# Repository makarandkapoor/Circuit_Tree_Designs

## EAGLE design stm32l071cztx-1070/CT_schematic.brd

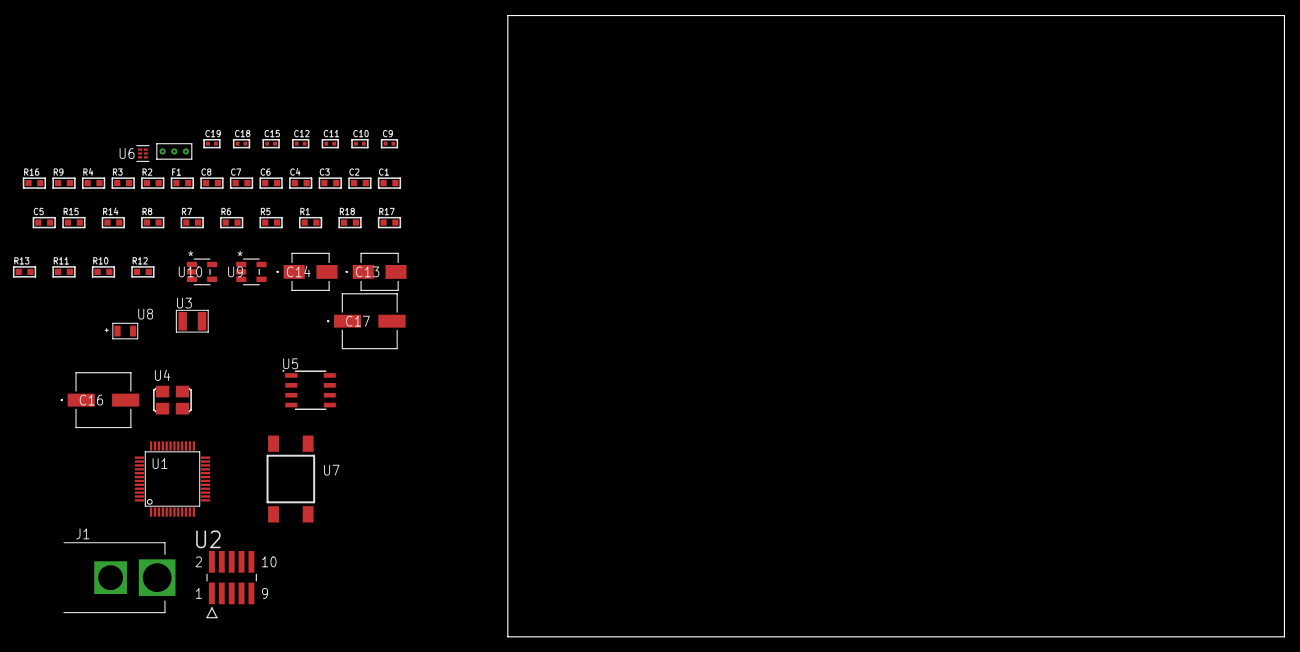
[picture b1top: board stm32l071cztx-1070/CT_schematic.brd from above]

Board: 2 copper layers, 100.0 x 80.0 mm, 50 parts (0 on the bottom side), 24 nets, no tracks yet.

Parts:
C1, C2, C3, C4, C6: 1e-07; C0603
C5: 4.7e-06; C0603
C7: 1e-08; C0603
C8: 1e-06; C0603
C9, C10: 1e-11; C0402
C11, C15: 1e-07; C0402
C12, C18, C19: 1e-08; C0402
C13: 1e-06; EXV-9B
C14: 2.2e-06; EXV-9B
C16, C17: 0.0001; EXV-9H
F1: 240.0; L0603
J1: PJ-037B; PJ-037B_PACKAGE
R1, R5, R6, R7, R8, R14, R15: 10000.0; R0603
R2: 1000.0; R0603
R3: 1600.5; R0603
R4: 4700.0; R0603
R9: 5.0; R0603
R10, R11, R13: 100000.0; R0603
R12: 164658.62; R0603
R16: 9100.0; R0603
R17: 680000.0; R0603
R18: 120000.0; R0603
U1: STM32L071CZT6; LQFP48
U2: FTSH-105-01-L-DV-K; SAMTEC_FTSH-105-01-L-DV-K
U3: ABS07-32.768KHZ-7-T
U4: ASFL1-25MHZ-NCS; ASFL1
U5: LP2954AIMX/NOPB; LP2954
U6: TPS3895ADRYR; SON-6
U7: 4-1437565-2; SW_4-1437565-2
U8: Q65110A2395; LGM67K-G1J2-24-Z
U9, U10: nc7sz125m5x; NC7SZ125M5X
U11: Dummy; DUMMY_PACKAGE_101

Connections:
CLK_CRYSTAL_U1_3: C9.1, U1.3, U3.1
CLK_CRYSTAL_U1_4: C10.1, U1.4, U3.2
CLK_U1_5: U1.5, U4.3
GND: C1.2, C2.2, C3.2, C4.2, C5.2, C6.2, C7.2, C8.2, C9.2, C10.2, C11.2, C12.2, C13.2, C14.2, C15.2, C16.2, C17.2, C18.2, C19.2, J1.2, R2.2, R5.2, R9.2, R13.2, R16.2, R18.2, U1.8, U1.23, U1.35, U1.47, U2.3, U2.5, U4.2, U5.4, U6.2, U8.C, U9.2, U9.3, U10.1, U10.3, U11.1
NET_U1_7: R4.1, U1.7, U10.4
NET_U1_9: C7.1, C8.1, F1.1, U1.9
NET_U1_44: R5.1, U1.44
NET_U1_45: R3.1, U1.45, U8.A
NET_U1_46: R1.1, U1.46, U7.3, U7.4
NET_U2_9: R9.1, U2.9
NET_U5_3: R11.1, U5.3
NET_U5_5: R10.1, U5.5
NET_U5_7: R12.2, R13.1, U5.7
NET_U6_1: R15.1, R16.1, U6.1
NET_U6_3: R17.2, R18.1, U6.3
NET_U6_4: R14.1, U6.4, U9.4, U10.2
NET_U7_1: R2.1, U7.1, U7.2
PROC_ADC_IN3: U1.13, U11.2
PROC_ADC_IN4: U1.14, U11.3
PROC_SYS_SWCLK: R7.1, U1.37, U2.4
PROC_SYS_SWDIO: R8.1, U1.34, U2.2
RST_OUT_U2_JTAG_RST_B: R6.1, U2.10, U9.1
VCC_S1_16V9: C13.1, C16.1, C17.1, J1.1, R11.2, U5.8
VCC_TIER1_3V3: C1.1, C2.1, C3.1, C4.1, C5.1, C6.1, C11.1, C12.1, C14.1, C15.1, C18.1, C19.1, F1.2, R1.2, R3.2, R4.2, R6.2, R7.2, R8.2, R10.2, R12.1, R14.2, R15.2, R17.1, U1.1, U1.24, U1.36, U1.48, U2.1, U4.4, U5.1, U6.6, U9.5, U10.5

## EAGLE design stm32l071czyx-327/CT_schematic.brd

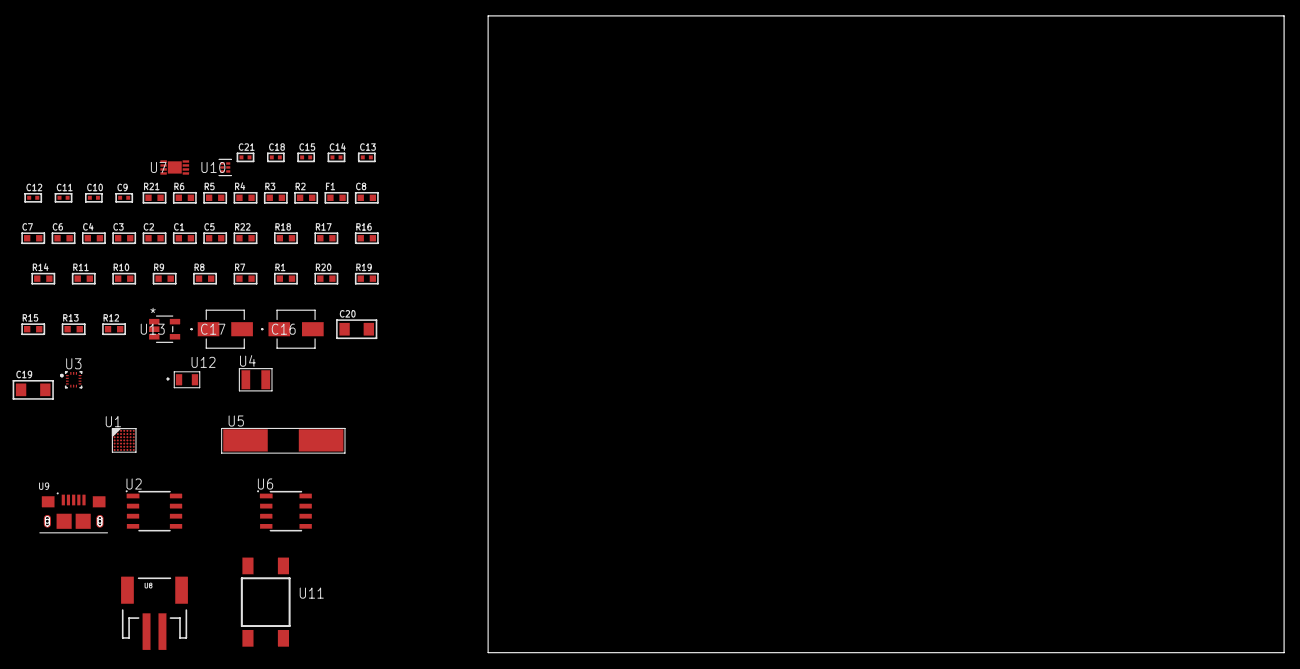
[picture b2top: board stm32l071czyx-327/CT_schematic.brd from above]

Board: 2 copper layers, 155.6 x 80.0 mm, 57 parts (0 on the bottom side), 30 nets, no tracks yet.

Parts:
C1, C2, C3, C4, C6: 1e-07; C0603
C5: 4.7e-06; C0603
C7: 1e-08; C0603
C8: 1e-06; C0603
C9, C10, C11, C12: 1e-11; C0402
C13, C21: 1e-08; C0402
C14, C15, C18: 1e-07; C0402
C16: 1e-06; EXV-9B
C17: 2.2e-06; EXV-9B
C19, C20: 1e-05; C1206
F1: 240.0; L0603
R1, R7, R8, R9, R10, R11, R16, R17, R22: 10000.0; R0603
R2: 1000.0; R0603
R3: 910.0; R0603
R4: 4700.0; R0603
R5, R6: 2200.0; R0603
R12, R13, R15: 100000.0; R0603
R14: 47000.0; R0603
R18: 82000.0; R0603
R19: 300000.0; R0603
R20: 120000.0; R0603
R21: 2000.0; R0603
U1: STM32L071CZY6; WLCSP49
U2: AT25320B-SSHL-T; SOIC-8
U3: BMC150; LGA14R35P5X6_200X200X100
U4: ABS07-32.768KHZ-7-T
U5: ABLS-25.000MHZ-B2F-T
U6: LP2954AIMX/NOPB; LP2954
U7: MCP73831T-2ACI/MC; DFN8_2X3MC
U8: S2B-PH-SM4-TB(LF)(SN); JST-2-SMD
U9: 10118193-0001LF; FCI_10118193-0001LF
U10: TPS3895ADRYR; SON-6
U11: 4-1437565-2; SW_4-1437565-2
U12: Q65110A2395; LGM67K-G1J2-24-Z
U13: nc7sz125m5x; NC7SZ125M5X

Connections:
CLK_CRYSTAL_U1_C6: C9.1, U1.C6, U4.1
CLK_CRYSTAL_U1_C7: C10.1, U1.C7, U4.2
CLK_CRYSTAL_U1_D6: C11.1, U1.D6, U5.1
CLK_CRYSTAL_U1_D7: C12.1, U1.D7, U5.2
GND: C1.2, C2.2, C3.2, C4.2, C5.2, C6.2, C7.2, C8.2, C9.2, C10.2, C11.2, C12.2, C13.2, C14.2, C15.2, C16.2, C17.2, C18.2, C19.2, C20.2, C21.2, R2.2, R7.2, R15.2, R18.2, R20.2, R21.2, U1.D4, U2.4, U3.1, U3.6, U3.7, U3.9, U6.4, U7.6, U7.9, U8.2, U9.5, U9.6, U9.7, U9.8, U9.9, U10.2, U12.C, U13.1, U13.3
INPUT_USBPOWER_5V: C19.1, R22.2, U7.1, U7.2, U9.1
NET_U1_A5: R7.1, U1.A5
NET_U1_A6: R6.1, U1.A6, U3.14
NET_U1_B4: R5.1, U1.B4, U3.11
NET_U1_D5: R4.1, U1.D5, U13.4
NET_U1_F7: C7.1, C8.1, F1.1, U1.E6, U1.F7
NET_U1_G6: R3.1, U1.G6, U12.A
NET_U1_G7: R1.1, U1.G7, U11.3, U11.4
NET_U2_3: R8.1, U2.3
NET_U2_7: R10.1, U2.7
NET_U6_3: R13.1, U6.3
NET_U6_5: R12.1, U6.5
NET_U6_7: R14.2, R15.1, U6.7
NET_U7_5: R22.1, U7.5
NET_U7_8: R21.1, U7.8
NET_U10_1: R17.1, R18.1, U10.1
NET_U10_3: R19.2, R20.1, U10.3
NET_U10_4: R16.1, U10.4, U13.2
NET_U11_1: R2.1, U11.1, U11.2
PROC_SPI1_MISO: U1.B3, U2.2
PROC_SPI1_MOSI: U1.A4, U2.5
PROC_SPI1_NSS: R9.1, U1.A2, U2.1
PROC_SPI1_SCK: U1.A3, U2.6
VCC_S1_3V7: C16.1, C20.1, R13.2, U6.8, U7.3, U7.4, U8.1
VCC_TIER1_1V8: C1.1, C2.1, C3.1, C4.1, C5.1, C6.1, C13.1, C14.1, C15.1, C17.1, C18.1, C21.1, F1.2, R1.2, R3.2, R4.2, R5.2, R6.2, R8.2, R9.2, R10.2, R11.1, R11.2, R12.2, R14.1, R16.2, R17.2, R19.1, U1.A1, U1.A7, U1.B6, U1.G2, U2.8, U3.8, U3.10, U3.12, U3.13, U6.1, U10.6, U13.5

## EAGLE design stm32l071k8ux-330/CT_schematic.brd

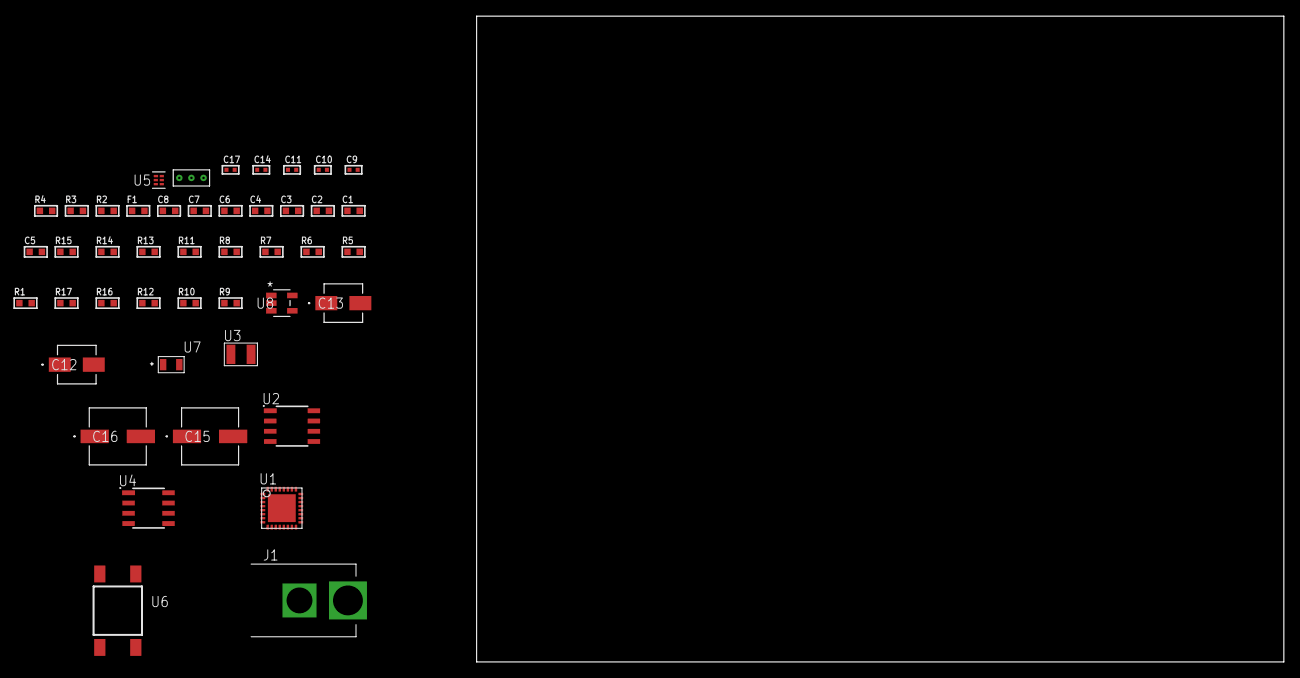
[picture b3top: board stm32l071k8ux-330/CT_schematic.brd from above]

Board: 2 copper layers, 100.0 x 80.0 mm, 45 parts (0 on the bottom side), 25 nets, no tracks yet.

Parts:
C1, C2, C3, C4, C6: 1e-07; C0603
C5: 4.7e-06; C0603
C7: 1e-08; C0603
C8: 1e-06; C0603
C9, C10: 1e-11; C0402
C11, C17: 1e-08; C0402
C12: 1e-06; EXV-9B
C13: 2.2e-06; EXV-9B
C14: 1e-07; C0402
C15, C16: 0.0001; EXV-9H
F1: 240.0; L0603
J1: PJ-037B; PJ-037B_PACKAGE
R1, R5, R6, R7, R8, R13, R14: 10000.0; R0603
R2: 1000.0; R0603
R3: 910.0; R0603
R4: 4700.0; R0603
R9, R10, R12: 100000.0; R0603
R11: 47000.0; R0603
R15: 82000.0; R0603
R16: 300000.0; R0603
R17: 120000.0; R0603
U1: STM32L071K8U6; UFQFPN32
U2: AT25512N-SH-T; SOIC-8
U3: ABS07-32.768KHZ-7-T
U4: LP2954AIMX/NOPB; LP2954
U5: TPS3895ADRYR; SON-6
U6: 4-1437565-2; SW_4-1437565-2
U7: Q65110A2395; LGM67K-G1J2-24-Z
U8: nc7sz125m5x; NC7SZ125M5X
U9: Dummy; DUMMY_PACKAGE_90

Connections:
CLK_CRYSTAL_U1_1: C9.1, U1.1, U3.1
CLK_CRYSTAL_U1_2: C10.1, U1.2, U3.2
GND: C1.2, C2.2, C3.2, C4.2, C5.2, C6.2, C7.2, C8.2, C9.2, C10.2, C11.2, C12.2, C13.2, C14.2, C15.2, C16.2, C17.2, J1.2, R2.2, R5.2, R12.2, R15.2, R17.2, U1.4, U1.16, U1.31, U1.EPAD, U2.4, U4.4, U5.2, U7.C, U8.1, U8.3, U9.1
NET_U1_3: R4.1, U1.3, U8.4
NET_U1_5: C7.1, C8.1, F1.1, U1.5
NET_U1_28: R3.1, U1.28, U7.A
NET_U1_29: R1.1, U1.29, U6.3, U6.4
NET_U1_30: R5.1, U1.30
NET_U2_3: R6.1, U2.3
NET_U2_7: R8.1, U2.7
NET_U4_3: R10.1, U4.3
NET_U4_5: R9.1, U4.5
NET_U4_7: R11.2, R12.1, U4.7
NET_U5_1: R14.1, R15.1, U5.1
NET_U5_3: R16.2, R17.1, U5.3
NET_U5_4: R13.1, U5.4, U8.2
NET_U6_1: R2.1, U6.1, U6.2
PROC_ADC_IN1: U1.7, U9.3
PROC_ADC_IN9: U1.15, U9.2
PROC_SPI1_MISO: U1.12, U2.2
PROC_SPI1_MOSI: U1.13, U2.5
PROC_SPI1_NSS: R7.1, U1.10, U2.1
PROC_SPI1_SCK: U1.11, U2.6
VCC_S1_16V2: C12.1, C15.1, C16.1, J1.1, R10.2, U4.8
VCC_TIER1_1V8: C1.1, C2.1, C3.1, C4.1, C5.1, C6.1, C11.1, C13.1, C14.1, C17.1, F1.2, R1.2, R3.2, R4.2, R6.2, R7.2, R8.2, R9.2, R11.1, R13.2, R14.2, R16.1, U1.17, U1.24, U1.32, U2.8, U4.1, U5.6, U8.5

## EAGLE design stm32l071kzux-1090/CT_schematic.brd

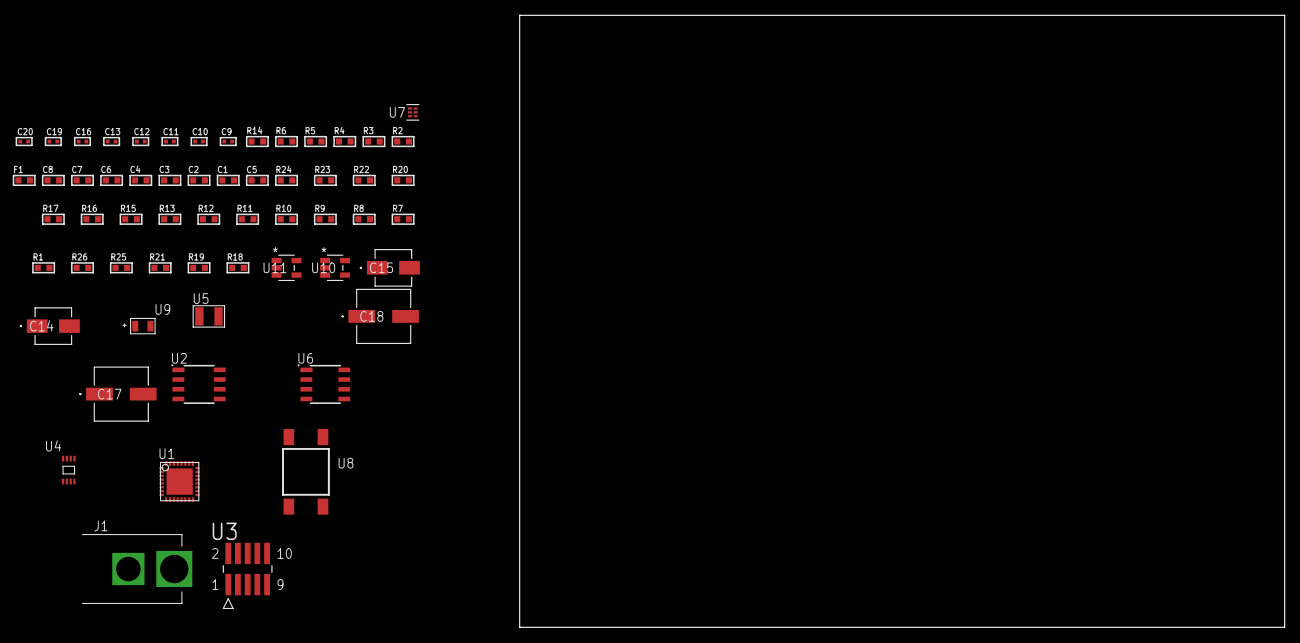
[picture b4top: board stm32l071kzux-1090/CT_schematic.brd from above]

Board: 2 copper layers, 100.0 x 80.0 mm, 59 parts (0 on the bottom side), 32 nets, no tracks yet.

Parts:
C1, C2, C3, C4, C6: 1e-07; C0603
C5: 4.7e-06; C0603
C7: 1e-08; C0603
C8: 1e-06; C0603
C9, C10: 1e-11; C0402
C11, C13, C19, C20: 1e-08; C0402
C12, C16: 1e-07; C0402
C14: 1e-06; EXV-9B
C15: 2.2e-06; EXV-9B
C17, C18: 0.0001; EXV-9H
F1: 240.0; L0603
J1: PJ-037B; PJ-037B_PACKAGE
R1, R7, R8, R9, R10, R11, R12, R13, R15, R16, R17, R22, R23: 10000.0; R0603
R2: 1000.0; R0603
R3: 910.0; R0603
R4: 4700.0; R0603
R5, R6: 2200.0; R0603
R14: 5.0; R0603
R18, R19, R21: 100000.0; R0603
R20: 47000.0; R0603
R24: 82000.0; R0603
R25: 300000.0; R0603
R26: 120000.0; R0603
U1: STM32L071KZU6; UFQFPN32
U2: AT25640B-SSHL-T; SOIC-8
U3: FTSH-105-01-L-DV-K; SAMTEC_FTSH-105-01-L-DV-K
U4: 24AA128T-I/MNY; TDFN-8/6MM
U5: ABS07-32.768KHZ-7-T
U6: LP2954AIMX/NOPB; LP2954
U7: TPS3895ADRYR; SON-6
U8: 4-1437565-2; SW_4-1437565-2
U9: Q65110A2395; LGM67K-G1J2-24-Z
U10, U11: nc7sz125m5x; NC7SZ125M5X

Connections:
CLK_CRYSTAL_U1_1: C9.1, U1.1, U5.1
CLK_CRYSTAL_U1_2: C10.1, U1.2, U5.2
GND: C1.2, C2.2, C3.2, C4.2, C5.2, C6.2, C7.2, C8.2, C9.2, C10.2, C11.2, C12.2, C13.2, C14.2, C15.2, C16.2, C17.2, C18.2, C19.2, C20.2, J1.2, R2.2, R7.2, R14.2, R15.2, R17.2, R21.2, R24.2, R26.2, U1.4, U1.16, U1.31, U1.EPAD, U2.4, U3.3, U3.5, U4.4, U4.7, U6.4, U7.2, U9.C, U10.2, U10.3, U11.1, U11.3
NET_U1_3: R4.1, U1.3, U11.4
NET_U1_5: C7.1, C8.1, F1.1, U1.5
NET_U1_19: R5.1, U1.19, U4.6
NET_U1_20: R6.1, U1.20, U4.5
NET_U1_28: R3.1, U1.28, U9.A
NET_U1_29: R1.1, U1.29, U8.3, U8.4
NET_U1_30: R7.1, U1.30
NET_U2_3: R8.1, U2.3
NET_U2_7: R10.1, U2.7
NET_U3_9: R14.1, U3.9
NET_U4_1: R15.1, U4.1
NET_U4_2: R16.1, U4.2
NET_U4_3: R17.1, U4.3
NET_U6_3: R19.1, U6.3
NET_U6_5: R18.1, U6.5
NET_U6_7: R20.2, R21.1, U6.7
NET_U7_1: R23.1, R24.1, U7.1
NET_U7_3: R25.2, R26.1, U7.3
NET_U7_4: R22.1, U7.4, U10.4, U11.2
NET_U8_1: R2.1, U8.1, U8.2
PROC_SPI1_MISO: U1.12, U2.2
PROC_SPI1_MOSI: U1.13, U2.5
PROC_SPI1_NSS: R9.1, U1.10, U2.1
PROC_SPI1_SCK: U1.11, U2.6
PROC_SYS_SWCLK: R12.1, U1.25, U3.4
PROC_SYS_SWDIO: R13.1, U1.23, U3.2
RST_OUT_U3_JTAG_RST_B: R11.1, U3.10, U10.1
VCC_S1_4V7: C14.1, C17.1, C18.1, J1.1, R19.2, U6.8
VCC_TIER1_1V8: C1.1, C2.1, C3.1, C4.1, C5.1, C6.1, C11.1, C12.1, C13.1, C15.1, C16.1, C19.1, C20.1, F1.2, R1.2, R3.2, R4.2, R5.2, R6.2, R8.2, R9.2, R10.2, R11.2, R12.2, R13.2, R16.2, R18.2, R20.1, R22.2, R23.2, R25.1, U1.17, U1.24, U1.32, U2.8, U3.1, U4.8, U6.1, U7.6, U10.5, U11.5

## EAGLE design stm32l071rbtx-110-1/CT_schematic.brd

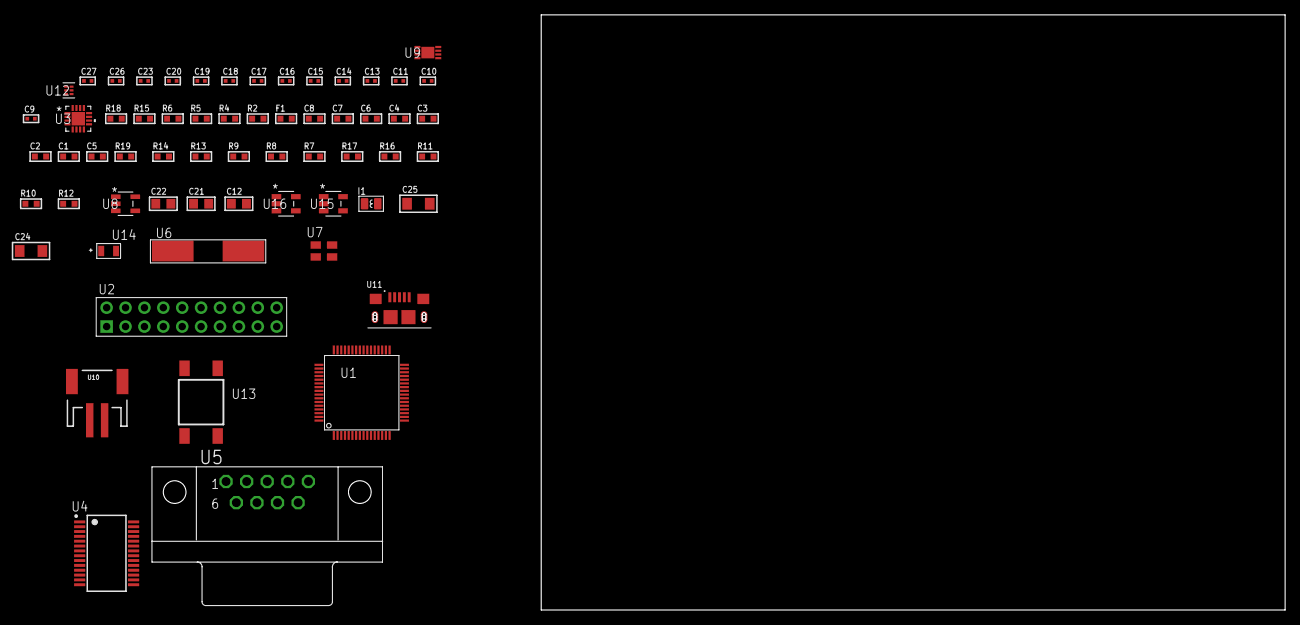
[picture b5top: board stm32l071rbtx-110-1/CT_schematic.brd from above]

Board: 2 copper layers, 122.6 x 80.0 mm, 62 parts (0 on the bottom side), 42 nets, no tracks yet.

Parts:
C1, C2, C3, C4, C6: 1e-07; C0603
C5: 4.7e-06; C0603
C7: 1e-08; C0603
C8: 1e-06; C0603
C9, C10: 1e-11; C0402
C11, C13, C14, C15, C16, C17, C18, C19, C23: 1e-07; C0402
C12: 4.7e-06; C0805
C20, C26, C27: 1e-08; C0402
C21, C22: 1e-05; C0805
C24, C25: 1e-05; C1206
F1: 240.0; L0603
I1: 3.3e-06; L0806
R2: 1000.0; R0603
R4: 4700.0; R0603
R5, R6: 2200.0; R0603
R7, R8, R9, R13, R14, R19: 10000.0; R0603
R10: 100000.0; R0603
R11: 220000.0; R0603
R12: 1000000.0; R0603
R15: 9100.0; R0603
R16: 680000.0; R0603
R17: 120000.0; R0603
R18: 2000.0; R0603
U1: STM32L071RBT6; LQFP64
U2: TST-110-05-T-D-RA
U3: MMA8451QT; QFN-16
U4: ST3241EBPR; SSOP-28
U5: 182-009-113R531; 182-009-MALE
U6: ABLS-25.000MHZ-B2F-T
U7: ASEK-32.768KHz-ECST; ASEK
U8: ltc3406es5; TSOT-23-5
U9: MCP73831T-2ACI/MC; DFN8_2X3MC
U10: S2B-PH-SM4-TB(LF)(SN); JST-2-SMD
U11: 10118193-0001LF; FCI_10118193-0001LF
U12: TPS3895ADRYR; SON-6
U13: 4-1437565-2; SW_4-1437565-2
U14: Q65110A2395; LGM67K-G1J2-24-Z
U15, U16: nc7sz125m5x; NC7SZ125M5X

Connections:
CLK_CRYSTAL_U1_5: C9.1, U1.5, U6.1
CLK_CRYSTAL_U1_6: C10.1, U1.6, U6.2
CLK_U1_3: U1.3, U7.3
GND: C1.2, C2.2, C3.2, C4.2, C5.2, C6.2, C7.2, C8.2, C9.2, C10.2, C11.2, C12.2, C13.2, C14.2, C15.2, C18.2, C19.2, C20.2, C21.2, C22.1, C22.2, C23.2, C24.2, C25.2, C26.2, C27.2, R2.2, R7.2, R11.2, R15.2, R17.2, R18.2, U1.12, U1.18, U1.31, U1.47, U1.63, U2.4, U2.6, U2.8, U2.10, U2.12, U2.14, U2.16, U2.18, U2.20, U3.5, U3.10, U3.12, U3.17, U4.23, U4.25, U5.5, U7.2, U8.2, U9.6, U9.9, U10.2, U11.5, U11.6, U11.7, U11.8, U11.9, U12.2, U14.C, U15.2, U15.3, U16.1, U16.3
INPUT_USBPOWER_5V: C24.1, R19.2, U9.1, U9.2, U11.1
NET_U1_7: R4.1, U1.7, U16.4
NET_U1_13: C7.1, C8.1, F1.1, U1.13
NET_U1_42: R5.1, U1.42, U3.4
NET_U1_43: R6.1, U1.43, U3.6
NET_U1_60: R7.1, U1.60
NET_U1_62: U13.3, U13.4
NET_U3_2: C14.1, U3.2
NET_U3_7: R9.1, U3.7
NET_U4_1: C17.1, U4.1
NET_U4_2: C17.2, U4.2
NET_U4_3: C19.1, U4.3
NET_U4_22: R10.1, U4.22
NET_U4_24: C16.2, U4.24
NET_U4_27: C18.1, U4.27
NET_U4_28: C16.1, U4.28
NET_U5_2: U4.4, U5.2
NET_U5_3: U4.9, U5.3
NET_U5_7: U4.5, U5.7
NET_U5_8: U4.10, U5.8
NET_U8_3: I1.1, U8.3
NET_U8_5: R11.1, R12.1, U8.5
NET_U8_ATNET_3: I1.2, R12.2
NET_U9_5: R19.1, U9.5
NET_U9_8: R18.1, U9.8
NET_U12_1: R14.1, R15.1, U12.1
NET_U12_3: R16.2, R17.1, U12.3
NET_U12_4: R13.1, U12.4, U15.4, U16.2
NET_U13_1: R2.1, U13.1, U13.2
PROC_LPUART1_CTS: U1.22, U4.13
PROC_LPUART1_RTS: U1.27, U4.18
PROC_LPUART1_RX: U1.8, U4.19
PROC_LPUART1_TX: U1.9, U4.14
PROC_SYS_SWCLK: U1.49, U2.9
PROC_SYS_SWDIO: U1.46, U2.7
RST_OUT_U2_SRESET_B: R8.1, U2.15, U15.1
VCC_S1_3V7: C21.1, C25.1, U8.4, U9.3, U9.4, U10.1
VCC_TIER1_3V3: C1.1, C2.1, C3.1, C4.1, C5.1, C6.1, C11.1, C12.1, C13.1, C15.1, C20.1, C22.2, C23.1, C26.1, C27.1, F1.2, I1.2, R4.2, R5.2, R6.2, R8.2, R9.2, R10.2, R12.2, R13.2, R14.2, R16.1, U1.1, U1.19, U1.32, U1.48, U1.64, U2.1, U3.1, U3.14, U4.26, U7.4, U12.6, U15.5, U16.5

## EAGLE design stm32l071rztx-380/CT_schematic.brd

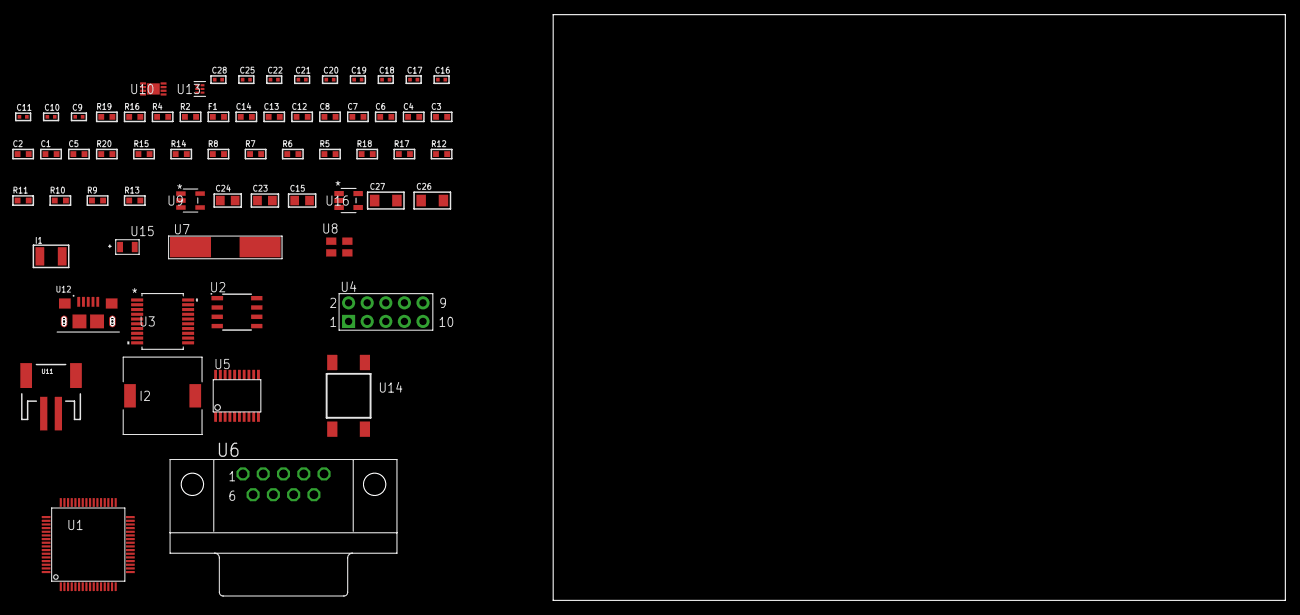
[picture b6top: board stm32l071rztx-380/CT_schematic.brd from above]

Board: 2 copper layers, 167.1 x 80.0 mm, 65 parts (0 on the bottom side), 56 nets, no tracks yet.

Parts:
C1, C2, C3, C4, C6: 1e-07; C0603
C5: 4.7e-06; C0603
C7: 1e-08; C0603
C8, C12, C13, C14: 1e-06; C0603
C9, C10: 1e-11; C0402
C11, C22, C28: 1e-08; C0402
C15: 4.7e-06; C0805
C16, C17, C18, C19, C20, C21, C25: 1e-07; C0402
C23, C24: 1e-05; C0805
C26, C27: 1e-05; C1206
F1: 240.0; L0603
I1: 1.5e-05; L1210
I2: 3.8e-06; DR1040
R2: 1000.0; R0603
R4: 4700.0; R0603
R5, R6, R7, R8, R14, R15, R20: 10000.0; R0603
R9, R10, R11: 100000.0; R0603
R12: 220000.0; R0603
R13: 1000000.0; R0603
R16: 9100.0; R0603
R17: 680000.0; R0603
R18: 120000.0; R0603
R19: 2000.0; R0603
U1: STM32L071RZT6; LQFP64
U2: AT25010B-SSHL-T; SOIC-8
U3: MAX3218EAP+T; SSOP-20
U4: HTSS-105-01-G-D
U5: SP3203ECY-L/TR; TSSOP20-I
U6: 182-009-113R531; 182-009-MALE
U7: ABLS-25.000MHZ-B2F-T
U8: ASEK-32.768KHz-ECST; ASEK
U9: ltc3406es5; TSOT-23-5
U10: MCP73831T-2ACI/MC; DFN8_2X3MC
U11: S2B-PH-SM4-TB(LF)(SN); JST-2-SMD
U12: 10118193-0001LF; FCI_10118193-0001LF
U13: TPS3895ADRYR; SON-6
U14: 4-1437565-2; SW_4-1437565-2
U15: Q65110A2395; LGM67K-G1J2-24-Z
U16: nc7sz125m5x; NC7SZ125M5X

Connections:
CLK_CRYSTAL_U1_5: C9.1, U1.5, U7.1
CLK_CRYSTAL_U1_6: C10.1, U1.6, U7.2
CLK_U1_3: U1.3, U8.3
GND: C1.2, C2.2, C3.2, C4.2, C5.2, C6.2, C7.2, C8.2, C9.2, C10.2, C11.2, C12.2, C13.2, C14.2, C16.2, C17.2, C20.2, C21.2, C22.2, C23.2, C24.1, C24.2, C25.2, C26.2, C27.2, C28.2, R2.2, R5.2, R12.2, R16.2, R18.2, R19.2, U1.12, U1.18, U1.31, U1.47, U1.63, U2.4, U3.5, U3.17, U3.20, U4.9, U5.18, U6.5, U8.2, U9.2, U10.6, U10.9, U11.2, U12.5, U12.6, U12.7, U12.8, U12.9, U13.2, U15.C, U16.1, U16.3
INPUT_USBPOWER_5V: C26.1, R20.2, U10.1, U10.2, U12.1
NET_U1_7: R4.1, U1.7, U16.4
NET_U1_13: C7.1, C8.1, F1.1, U1.13
NET_U1_60: R5.1, U1.60
NET_U1_62: U14.3, U14.4
NET_U2_3: R6.1, U2.3
NET_U2_7: R8.1, U2.7
NET_U3_1: I1.1, U3.1
NET_U3_2: R9.1, U3.2
NET_U3_3: R10.1, U3.3
NET_U3_4: R11.1, U3.4
NET_U3_15: C14.1, U3.15
NET_U3_16: C15.2, U3.16
NET_U3_18: C15.1, U3.18
NET_U3_19: C13.1, U3.19
NET_U4_3: U3.12, U4.3
NET_U4_4: U3.11, U4.4
NET_U4_5: U3.14, U4.5
NET_U4_6: U3.13, U4.6
NET_U5_1: C18.1, U5.1
NET_U5_2: C20.1, U5.2
NET_U5_3: C18.2, U5.3
NET_U5_4: C19.1, U5.4
NET_U5_5: C19.2, U5.5
NET_U5_6: C21.1, U5.6
NET_U6_2: U5.14, U6.2
NET_U6_3: U5.17, U6.3
NET_U6_7: U5.13, U6.7
NET_U6_8: U5.16, U6.8
NET_U9_3: I2.1, U9.3
NET_U9_5: R12.1, R13.1, U9.5
NET_U9_ATNET_3: I2.2, R13.2
NET_U10_5: R20.1, U10.5
NET_U10_8: R19.1, U10.8
NET_U13_1: R15.1, R16.1, U13.1
NET_U13_3: R17.2, R18.1, U13.3
NET_U13_4: R14.1, U13.4, U16.2
NET_U14_1: R2.1, U14.1, U14.2
PROC_LPUART1_CTS: U1.22, U3.8
PROC_LPUART1_RTS: U1.27, U3.10
PROC_LPUART1_RX: U1.8, U3.9
PROC_LPUART1_TX: U1.9, U3.7
PROC_SPI1_MISO: U1.56, U2.2
PROC_SPI1_MOSI: U1.23, U2.5
PROC_SPI1_NSS: R7.1, U1.20, U2.1
PROC_SPI1_SCK: U1.21, U2.6
PROC_USART1_CTS: U1.44, U5.8
PROC_USART1_RTS: U1.45, U5.10
PROC_USART1_RX: U1.43, U5.11
PROC_USART1_TX: U1.42, U5.7
VCC_S1_3V7: C23.1, C27.1, U9.4, U10.3, U10.4, U11.1
VCC_TIER1_3V3: C1.1, C2.1, C3.1, C4.1, C5.1, C6.1, C11.1, C12.1, C16.1, C17.1, C22.1, C24.2, C25.1, C28.1, F1.2, I1.2, I2.2, R4.2, R6.2, R7.2, R8.2, R9.2, R10.2, R11.2, R13.2, R14.2, R15.2, R17.1, U1.1, U1.19, U1.32, U1.48, U1.64, U2.8, U3.6, U5.12, U5.19, U8.4, U13.6, U16.5

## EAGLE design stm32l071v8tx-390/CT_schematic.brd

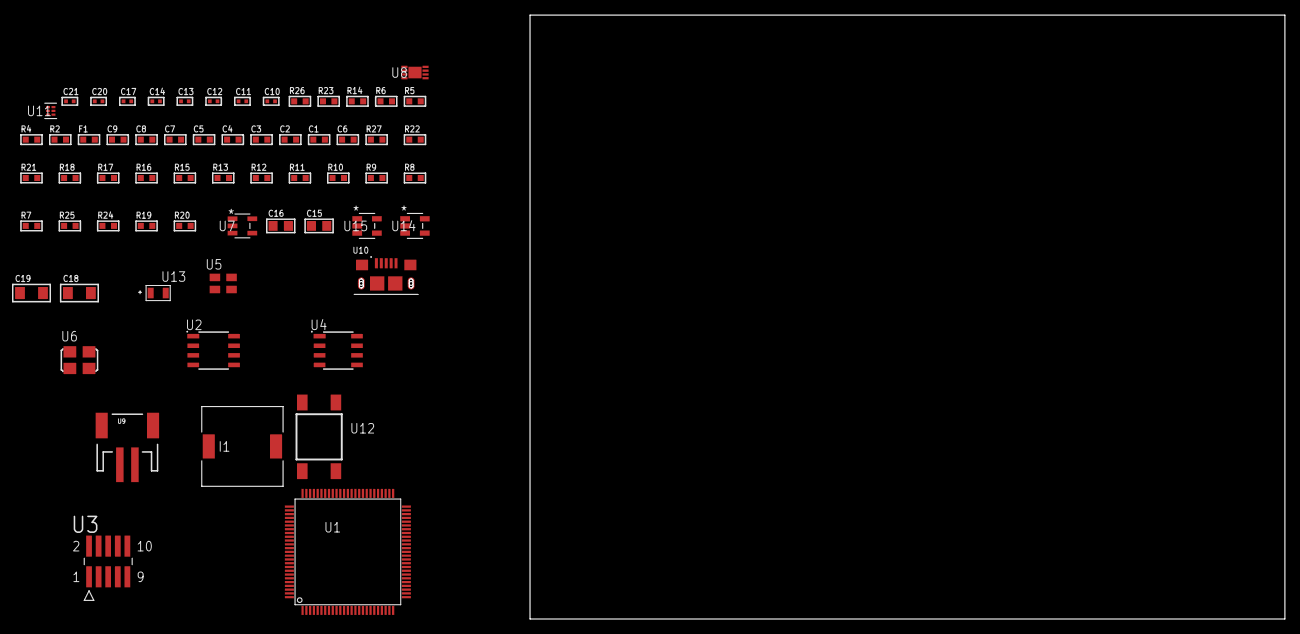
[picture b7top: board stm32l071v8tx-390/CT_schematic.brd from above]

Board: 2 copper layers, 122.6 x 80.0 mm, 63 parts (0 on the bottom side), 35 nets, no tracks yet.

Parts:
C1, C2, C3, C4, C5, C7: 1e-07; C0603
C6: 4.7e-06; C0603
C8: 1e-08; C0603
C9: 1e-06; C0603
C10, C12, C13, C14, C20, C21: 1e-08; C0402
C11, C17: 1e-07; C0402
C15, C16: 1e-05; C0805
C18, C19: 1e-05; C1206
F1: 240.0; L0603
I1: 3.8e-06; DR1040
R2: 1000.0; R0603
R4: 4700.0; R0603
R5, R6: 2200.0; R0603
R7, R8, R9, R10, R11, R12, R13, R15, R16, R17, R18, R21, R22, R27: 10000.0; R0603
R14: 5.0; R0603
R19: 220000.0; R0603
R20: 1000000.0; R0603
R23: 9100.0; R0603
R24: 680000.0; R0603
R25: 120000.0; R0603
R26: 2000.0; R0603
U1: STM32L071V8T6; LQFP100
U2: AT25256B-SSHL-T; SOIC-8
U3: FTSH-105-01-L-DV-K; SAMTEC_FTSH-105-01-L-DV-K
U4: AT24C02D-SSHM-T; AT24C02D
U5: ASEK-32.768KHz-ECST; ASEK
U6: ASFL1-25MHZ-NCS; ASFL1
U7: ltc3406es5; TSOT-23-5
U8: MCP73831T-2ACI/MC; DFN8_2X3MC
U9: S2B-PH-SM4-TB(LF)(SN); JST-2-SMD
U10: 10118193-0001LF; FCI_10118193-0001LF
U11: TPS3895ADRYR; SON-6
U12: 4-1437565-2; SW_4-1437565-2
U13: Q65110A2395; LGM67K-G1J2-24-Z
U14, U15: nc7sz125m5x; NC7SZ125M5X

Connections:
CLK_U1_8: U1.8, U5.3
CLK_U1_12: U1.12, U6.3
GND: C1.2, C2.2, C3.2, C4.2, C5.2, C6.2, C7.2, C8.2, C9.2, C10.2, C11.2, C12.2, C13.2, C14.2, C15.2, C16.1, C16.2, C17.2, C18.2, C19.2, C20.2, C21.2, R2.2, R7.2, R14.2, R15.2, R17.2, R18.2, R19.2, R23.2, R25.2, R26.2, U1.19, U1.20, U1.27, U1.49, U1.74, U1.99, U2.4, U3.3, U3.5, U4.4, U5.2, U6.2, U7.2, U8.6, U8.9, U9.2, U10.5, U10.6, U10.7, U10.8, U10.9, U11.2, U13.C, U14.2, U14.3, U15.1, U15.3
INPUT_USBPOWER_5V: C18.1, R27.2, U8.1, U8.2, U10.1
NET_U1_14: R4.1, U1.14, U15.4
NET_U1_22: C8.1, C9.1, F1.1, U1.21, U1.22
NET_U1_68: R5.1, U1.68, U4.6
NET_U1_69: R6.1, U1.69, U4.5
NET_U1_94: R7.1, U1.94
NET_U1_98: U12.3, U12.4
NET_U2_3: R8.1, U2.3
NET_U2_7: R10.1, U2.7
NET_U3_9: R14.1, U3.9
NET_U4_1: R16.1, U4.1
NET_U4_2: R17.1, U4.2
NET_U4_3: R18.1, U4.3
NET_U4_7: R15.1, U4.7
NET_U7_3: I1.1, U7.3
NET_U7_5: R19.1, R20.1, U7.5
NET_U7_ATNET_3: I1.2, R20.2
NET_U8_5: R27.1, U8.5
NET_U8_8: R26.1, U8.8
NET_U11_1: R22.1, R23.1, U11.1
NET_U11_3: R24.2, R25.1, U11.3
NET_U11_4: R21.1, U11.4, U14.4, U15.2
NET_U12_1: R2.1, U12.1, U12.2
PROC_SPI1_MISO: U1.31, U2.2
PROC_SPI1_MOSI: U1.32, U2.5
PROC_SPI1_NSS: R9.1, U1.29, U2.1
PROC_SPI1_SCK: U1.30, U2.6
PROC_SYS_SWCLK: R12.1, U1.76, U3.4
PROC_SYS_SWDIO: R13.1, U1.72, U3.2
RST_OUT_U3_JTAG_RST_B: R11.1, U3.10, U14.1
VCC_S1_3V7: C15.1, C19.1, U7.4, U8.3, U8.4, U9.1
VCC_TIER1_3V3: C1.1, C2.1, C3.1, C4.1, C5.1, C6.1, C7.1, C10.1, C11.1, C12.1, C13.1, C14.1, C16.2, C17.1, C20.1, C21.1, F1.2, I1.2, R4.2, R5.2, R6.2, R8.2, R9.2, R10.2, R11.2, R12.2, R13.2, R16.2, R20.2, R21.2, R22.2, R24.1, U1.6, U1.28, U1.50, U1.73, U1.75, U1.100, U2.8, U3.1, U4.8, U5.4, U6.4, U11.6, U14.5, U15.5

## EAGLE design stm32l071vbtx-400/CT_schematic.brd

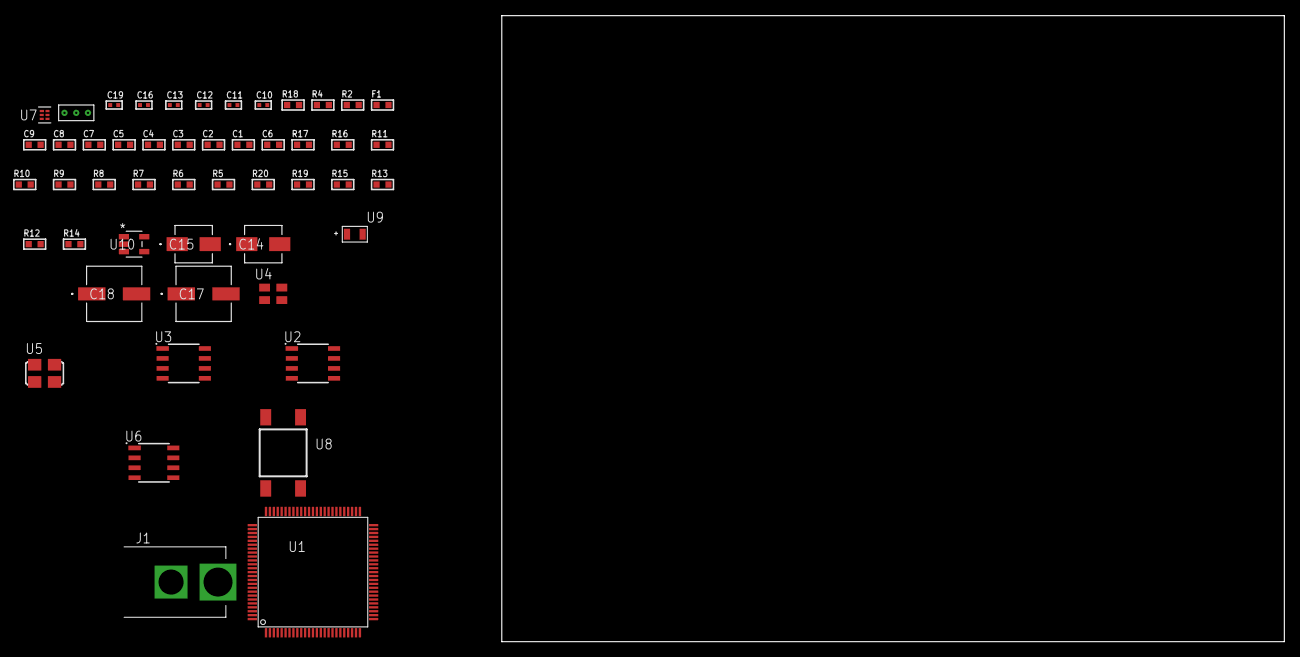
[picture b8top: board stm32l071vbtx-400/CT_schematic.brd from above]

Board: 2 copper layers, 100.0 x 80.0 mm, 50 parts (0 on the bottom side), 30 nets, no tracks yet.

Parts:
C1, C2, C3, C4, C5, C7: 1e-07; C0603
C6: 4.7e-06; C0603
C8: 1e-08; C0603
C9: 1e-06; C0603
C10, C11, C12, C13, C19: 1e-08; C0402
C14: 1e-06; EXV-9B
C15: 2.2e-06; EXV-9B
C16: 1e-07; C0402
C17, C18: 0.0001; EXV-9H
F1: 240.0; L0603
J1: PJ-037B; PJ-037B_PACKAGE
R2: 1000.0; R0603
R4: 4700.0; R0603
R5, R6, R7, R8, R9, R10, R11, R16, R17: 10000.0; R0603
R12, R13, R15: 100000.0; R0603
R14: 164658.62; R0603
R18: 9100.0; R0603
R19: 680000.0; R0603
R20: 120000.0; R0603
U1: STM32L071VBT6; LQFP100
U2: AT25040B-SSHL-T; SOIC-8
U3: AT25M02-SSHD-T; SOIC-8
U4: ASEK-32.768KHz-ECST; ASEK
U5: ASFL1-25MHZ-NCS; ASFL1
U6: LP2954AIMX/NOPB; LP2954
U7: TPS3895ADRYR; SON-6
U8: 4-1437565-2; SW_4-1437565-2
U9: Q65110A2395; LGM67K-G1J2-24-Z
U10: nc7sz125m5x; NC7SZ125M5X
U11: Dummy; DUMMY_PACKAGE_110

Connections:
CLK_U1_8: U1.8, U4.3
CLK_U1_12: U1.12, U5.3
GND: C1.2, C2.2, C3.2, C4.2, C5.2, C6.2, C7.2, C8.2, C9.2, C10.2, C11.2, C12.2, C13.2, C14.2, C15.2, C16.2, C17.2, C18.2, C19.2, J1.2, R2.2, R5.2, R15.2, R18.2, R20.2, U1.19, U1.20, U1.27, U1.49, U1.74, U1.99, U2.4, U3.4, U4.2, U5.2, U6.4, U7.2, U9.C, U10.1, U10.3, U11.1
NET_U1_14: R4.1, U1.14, U10.4
NET_U1_22: C8.1, C9.1, F1.1, U1.21, U1.22
NET_U1_94: R5.1, U1.94
NET_U1_98: U8.3, U8.4
NET_U2_3: R6.1, U2.3
NET_U2_7: R8.1, U2.7
NET_U3_3: R9.1, U3.3
NET_U3_7: R11.1, U3.7
NET_U6_3: R13.1, U6.3
NET_U6_5: R12.1, U6.5
NET_U6_7: R14.2, R15.1, U6.7
NET_U7_1: R17.1, R18.1, U7.1
NET_U7_3: R19.2, R20.1, U7.3
NET_U7_4: R16.1, U7.4, U10.2
NET_U8_1: R2.1, U8.1, U8.2
PROC_SPI1_MISO: U1.31, U3.2
PROC_SPI1_MOSI: U1.32, U3.5
PROC_SPI1_NSS: R10.1, U1.29, U3.1
PROC_SPI1_SCK: U1.30, U3.6
PROC_SPI2_MISO: U1.17, U2.2
PROC_SPI2_MOSI: U1.18, U2.5
PROC_SPI2_NSS: R7.1, U1.51, U2.1
PROC_SPI2_SCK: U1.47, U2.6
PROC_TIM2_CH1: U1.23, U11.3
PROC_TIM2_CH3: U1.25, U11.2
VCC_S1_10V2: C14.1, C17.1, C18.1, J1.1, R13.2, U6.8
VCC_TIER1_3V3: C1.1, C2.1, C3.1, C4.1, C5.1, C6.1, C7.1, C10.1, C11.1, C12.1, C13.1, C15.1, C16.1, C19.1, F1.2, R4.2, R6.2, R7.2, R8.2, R9.2, R10.2, R11.2, R12.2, R14.1, R16.2, R17.2, R19.1, U1.6, U1.28, U1.50, U1.73, U1.75, U1.100, U2.8, U3.8, U4.4, U5.4, U6.1, U7.6, U10.5
